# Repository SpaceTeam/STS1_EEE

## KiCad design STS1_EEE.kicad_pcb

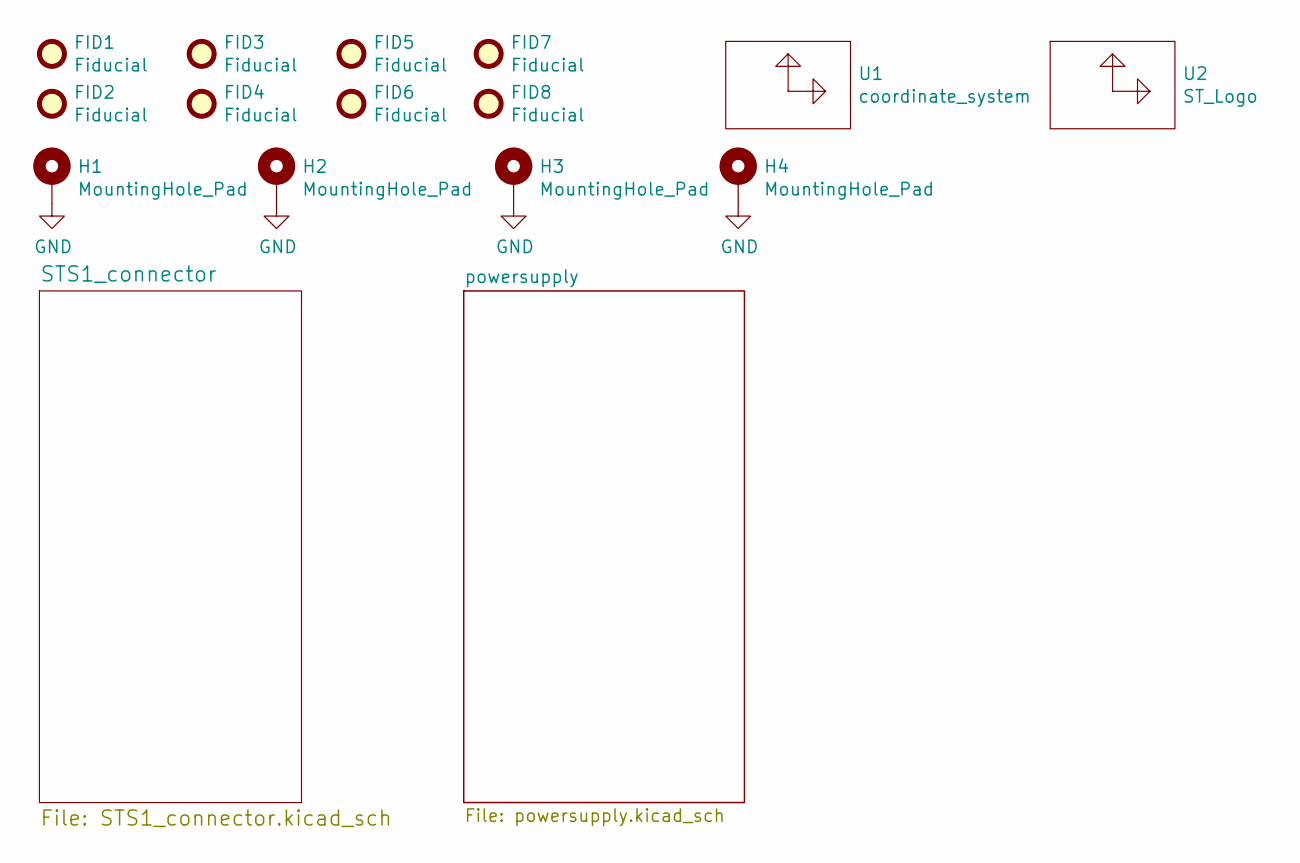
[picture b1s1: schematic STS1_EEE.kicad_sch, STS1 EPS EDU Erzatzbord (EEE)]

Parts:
FID1, FID2, FID3, FID4, FID5, FID6, FID7, FID8: Fiducial; Fiducial_0.75mm_Mask1.5mm
H1, H2, H3, H4: MountingHole_Pad; MountingHole_4.3mm_M4_Pad_Via
U1: coordinate_system; Coordinates
U2: ST_Logo; STLogo_7x8

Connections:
GND: H1.1 (1_1), H2.1 (1_1), H3.1 (1_1), H4.1 (1_1); also elsewhere on the board

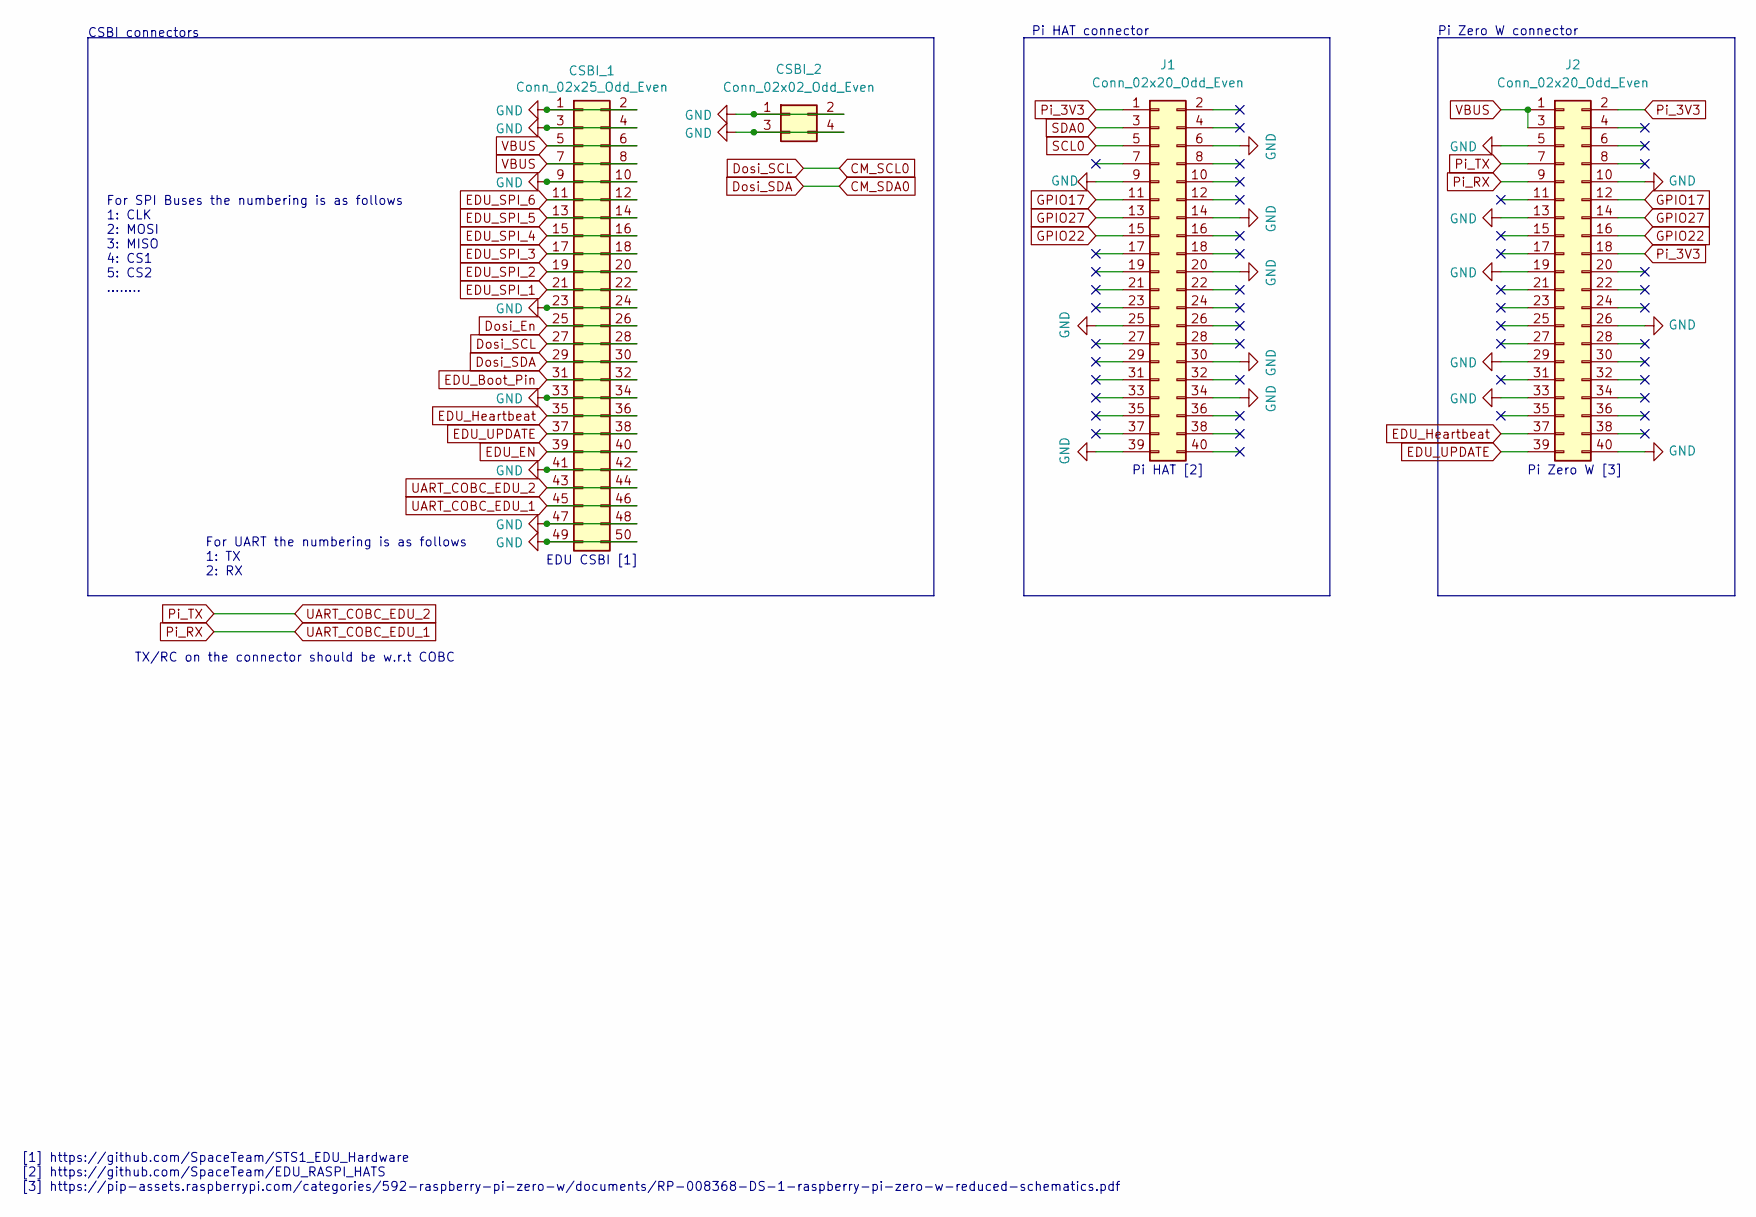
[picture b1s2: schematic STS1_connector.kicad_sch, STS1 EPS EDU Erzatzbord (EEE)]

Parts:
CSBI_1: Conn_02x25_Odd_Even; PinHeader_2x25_P2.00mm_Vertical
CSBI_2: Conn_02x02_Odd_Even; PinHeader_2x02_P2.00mm_Vertical
J1, J2: Conn_02x20_Odd_Even; PinHeader_2x20_P2.54mm_Vertical

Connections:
CM_SCL0: CSBI_1.27, CSBI_1.28
CM_SDA0: CSBI_1.29, CSBI_1.30
Dosi_En: CSBI_1.25, CSBI_1.26
EDU_Boot_Pin: CSBI_1.31, CSBI_1.32
EDU_EN: CSBI_1.39, CSBI_1.40; also elsewhere on the board
EDU_Heartbeat: CSBI_1.35, CSBI_1.36, J2.37
EDU_SPI_1: CSBI_1.21, CSBI_1.22
EDU_SPI_2: CSBI_1.19, CSBI_1.20
EDU_SPI_3: CSBI_1.17, CSBI_1.18
EDU_SPI_4: CSBI_1.15, CSBI_1.16
EDU_SPI_5: CSBI_1.13, CSBI_1.14
EDU_SPI_6: CSBI_1.11, CSBI_1.12
EDU_UPDATE: CSBI_1.37, CSBI_1.38, J2.39
GND: CSBI_1.1, CSBI_1.2, CSBI_1.3, CSBI_1.4, CSBI_1.9, CSBI_1.10, CSBI_1.23, CSBI_1.24, CSBI_1.33, CSBI_1.34, CSBI_1.41, CSBI_1.42, CSBI_1.47, CSBI_1.48, CSBI_1.49, CSBI_1.50, CSBI_2.1, CSBI_2.2, CSBI_2.3, CSBI_2.4, J1.6, J1.9, J1.14, J1.20, J1.25, J1.30, J1.34, J1.39, J2.5, J2.10, J2.13, J2.19, J2.26, J2.29, J2.33, J2.40; also elsewhere on the board
GPIO17: J1.11, J2.12
GPIO22: J1.15, J2.16
GPIO27: J1.13, J2.14
Pi_3V3: J1.1, J2.2, J2.18; also elsewhere on the board
Pi_RX: CSBI_1.45, CSBI_1.46, J2.9
Pi_TX: CSBI_1.43, CSBI_1.44, J2.7
SCL0: J1.5
SDA0: J1.3
VBUS: CSBI_1.5, CSBI_1.6, CSBI_1.7, CSBI_1.8, J2.1, J2.3; also elsewhere on the board

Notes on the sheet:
Pi Zero W connector
For SPI Buses the numbering is as follows 1: CLK 2: MOSI 3: MISO 4: CS1 5: CS2 ........
EDU CSBI [1]
CSBI connectors
TX/RC on the connector should be w.r.t COBC
Pi HAT connector
For UART the numbering is as follows 1: TX 2: RX
Pi Zero W [3]
[1] https://github.com/SpaceTeam/STS1_EDU_Hardware [2] https://github.com/SpaceTeam/EDU_RASPI_HATS [3] https://pip-assets.raspberrypi.com/categories/592-raspberry-pi-zero-w/documents/RP-008368-DS-1-raspberry-pi-zero-w-reduced-schematics.pdf
Pi HAT [2]

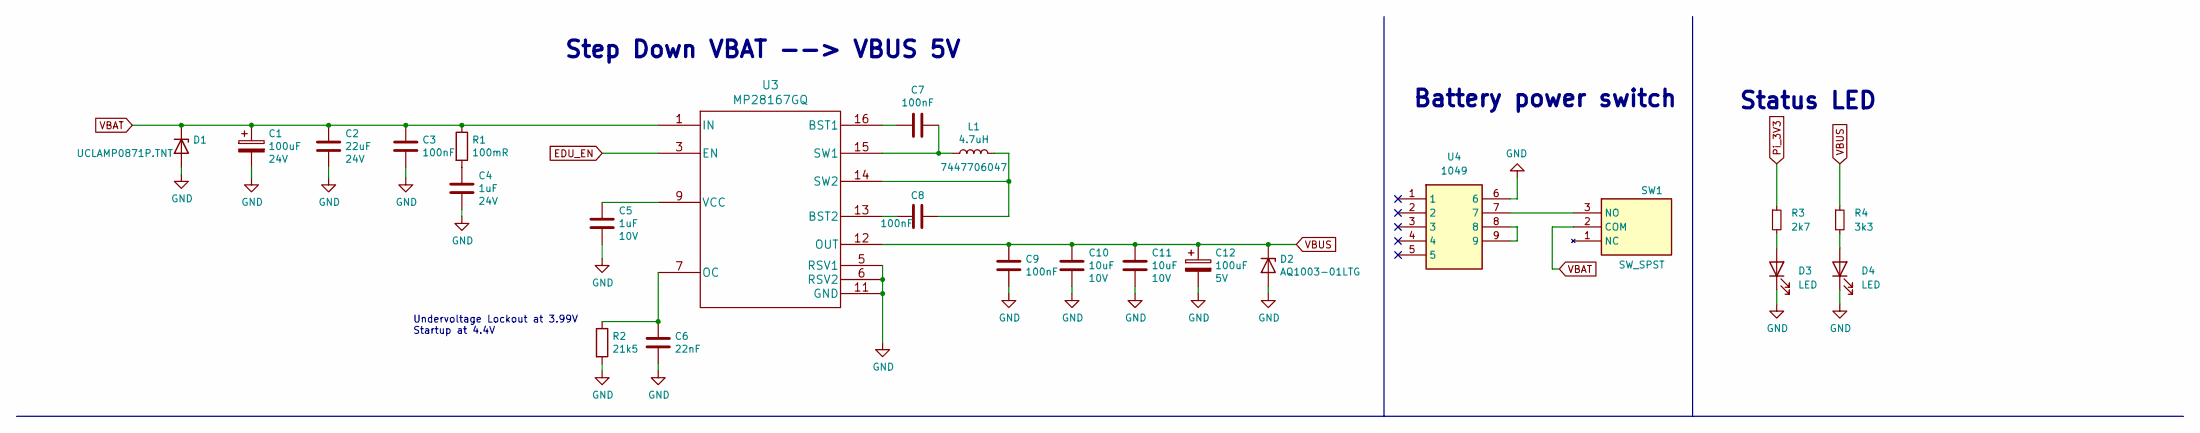
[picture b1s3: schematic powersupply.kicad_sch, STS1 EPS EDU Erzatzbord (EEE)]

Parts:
C1: 100uF; CP_EIA-7343-43_Kemet-X; Voltage 24V
C2: 22uF; C_1206_3216Metric; Voltage 24V
C3, C7, C8, C9: 100nF; C_0603_1608Metric
C4: 1uF; C_0805_2012Metric; Voltage 24V
C5: 1uF; C_0805_2012Metric; Voltage 10V
C6: 22nF; C_0603_1608Metric
C10, C11: 10uF; C_0805_2012Metric; Voltage 10V
C12: 100uF; CP_EIA-7343-43_Kemet-X; Voltage 5V
D1: UCLAMP0871P.TNT; SGP1610N2
D2: AQ1003-01LTG; D_SOD-523
D3, D4: LED; LED_0603_1608Metric_Pad1.05x0.95mm_HandSolder
L1: 4.7uH; L_12x12mm_H6mm; Part 7447706047
R1: 100mR; R_0603_1608Metric
R2: 21k5; R_0603_1608Metric
R3: 2k7; R_0603_1608Metric_Pad0.98x0.95mm_HandSolder
R4: 3k3; R_0603_1608Metric_Pad0.98x0.95mm_HandSolder
SW1: SW_SPST; CS12ANW03; Mouser Part Number 633-CS12ANW03
U3: MP28167GQ; MP28167_QFN16
U4: 1049; Mouser Part Number 534-1049

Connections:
EDU_EN: U3.3 (EN); also elsewhere on the board
GND: C1.2, C2.2, C3.2, C4.2, C5.2, C6.2, C9.2, C10.2, C11.2, C12.2, D1.2 (A), D2.2 (A), D3.1 (K), D4.1 (K), R2.2, U3.2 (GND), U3.4 (NC), U3.5 (RSV1), U3.6 (RSV2), U3.8 (NC), U3.10 (AGND), U3.11 (GND), U4.6; also elsewhere on the board
unnamed: C4.1, R1.2
unnamed: D3.2 (A), R3.2
unnamed: D4.2 (A), R4.2
unnamed: SW1.3 (NO), U4.7
unnamed: C7.2, U3.16 (BST1)
unnamed: C8.2, U3.13 (BST2)
unnamed: C6.1, R2.1, U3.7 (OC)
unnamed: C7.1, L1.1, U3.15 (SW1)
unnamed: C8.1, L1.2, U3.14 (SW2)
unnamed: C5.1, U3.9 (VCC)
unnamed: U4.8, U4.9
Pi_3V3: R3.1; also elsewhere on the board
VBAT: C1.1, C2.1, C3.1, D1.1 (K), R1.1, SW1.2 (COM), U3.1 (IN)
VBUS: C9.1, C10.1, C11.1, C12.1, D2.1 (K), R4.1, U3.12 (OUT); also elsewhere on the board

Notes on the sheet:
Battery power switch
Status LED
Step Down VBAT --> VBUS 5V
Undervoltage Lockout at 3.99V Startup at 4.4V

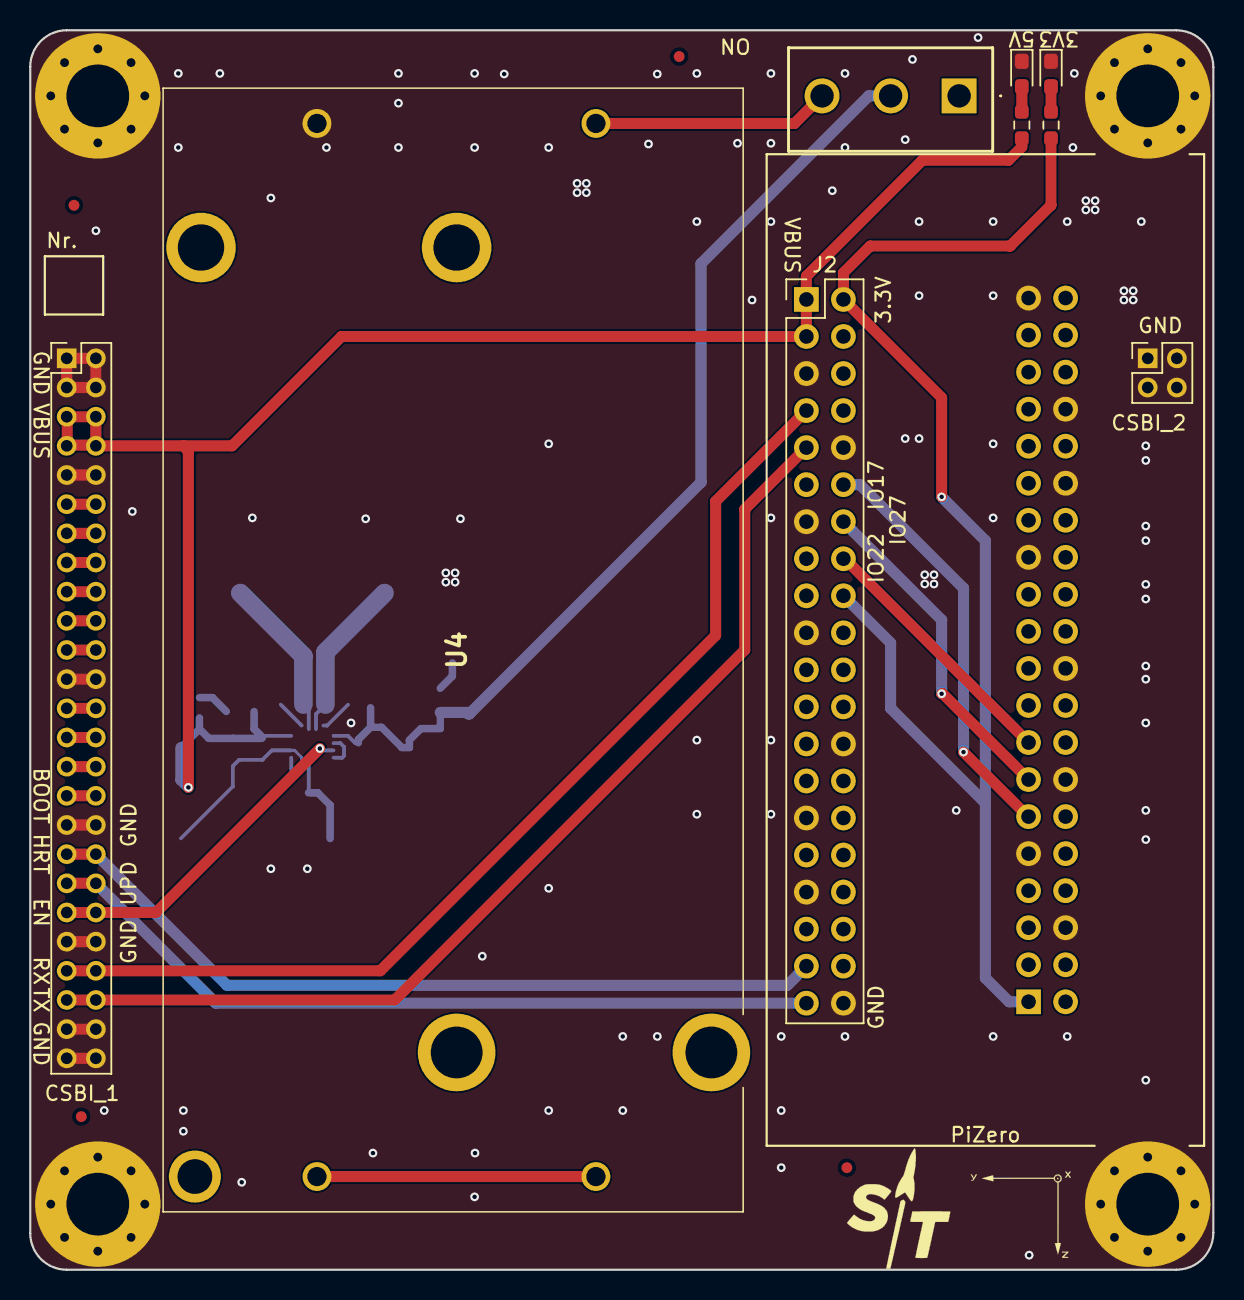
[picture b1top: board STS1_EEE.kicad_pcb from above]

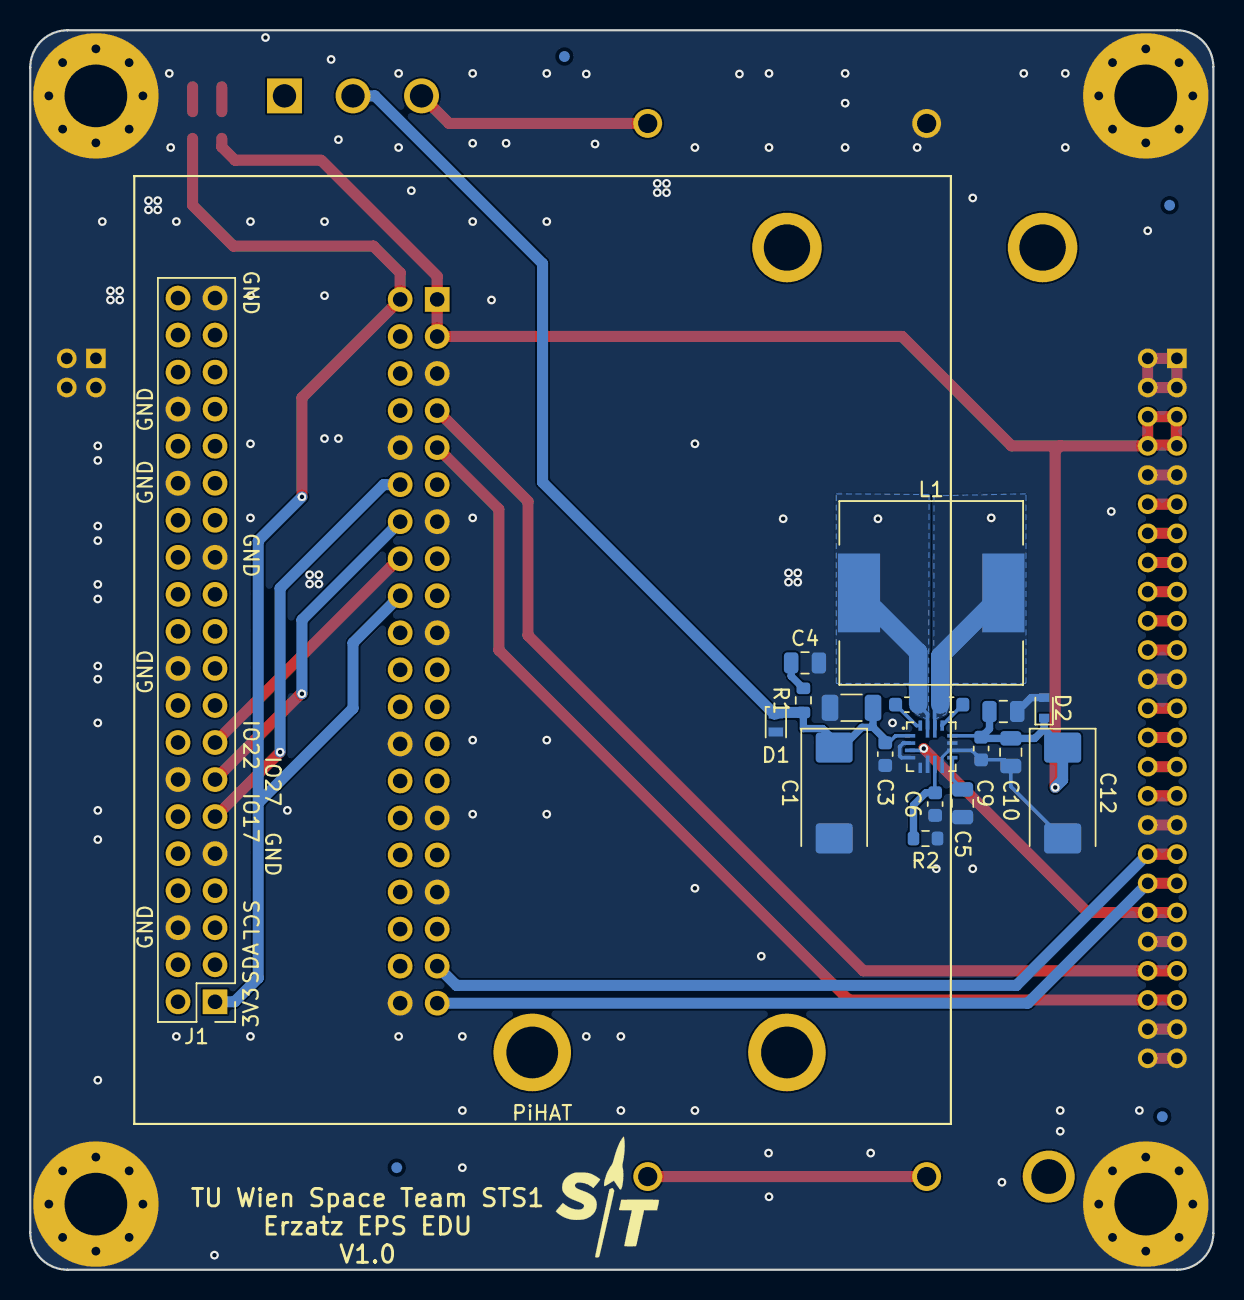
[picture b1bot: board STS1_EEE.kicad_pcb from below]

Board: 2 copper layers, 81.1 x 85.0 mm, 43 parts (24 on the bottom side), 33 nets.

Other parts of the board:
U2#2: ST_Logo; STLogo_7x8
